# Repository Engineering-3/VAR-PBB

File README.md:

# VAR-PBB
Power Bus Board, but for variable uses

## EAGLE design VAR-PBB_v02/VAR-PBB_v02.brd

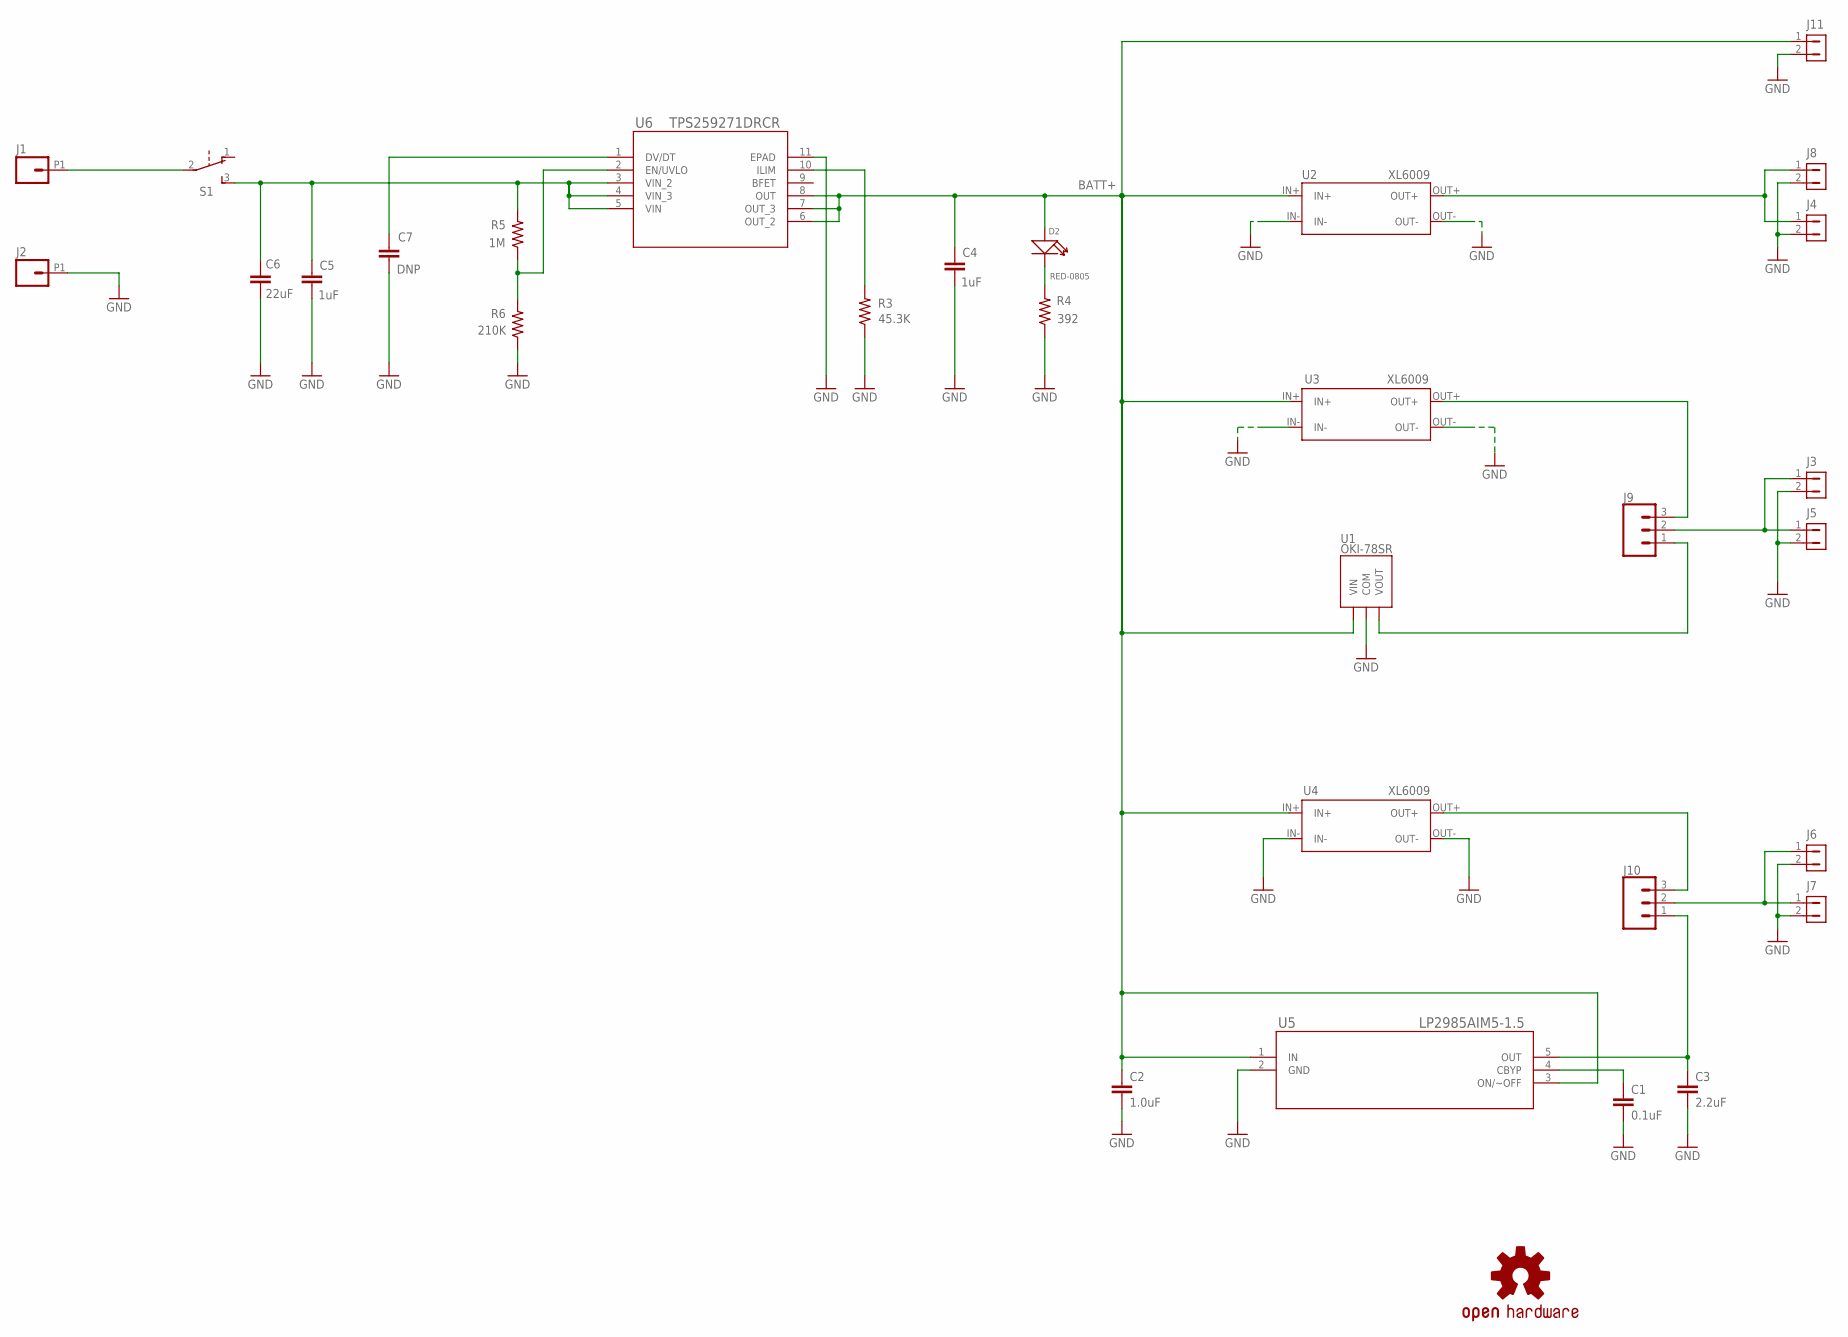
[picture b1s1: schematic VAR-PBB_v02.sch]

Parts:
C1: 0.1uF; 0603
C2: 1.0uF; 0603
C3: 2.2uF; 0603
C4, C5: 1uF; 0603
C6: 22uF; 1210
C7: DNP; 0603
D2: RED-0805; LED-0805
J1, J2: ANDERSON_POWER_POLE
J3, J4, J5, J6, J7, J8, J11: CON1X2_SHROUDED; HEADER_1X2_SHROUDED
J9, J10: CONN_03; 1X03
LOGO2: OSHW-LOGOM; OSHW-LOGO-M
R3: 45.3K; 0603
R4: 392; 0603
R5: 1M; 0603
R6: 210K; 0603
S1: SWITCH_SLIDE_ON_ON; SWITCH_SLIDE_RA
U1: OKI-78SR; OKI-78SR_REGULATOR_HORIZONTAL
U2, U3, U4: XL6009; XL6009_MODULE
U5: LP2985AIM5-1.5; MF05A
U6: TPS259271DRCR; DRC10_1P65X2P40
U$6: ROHS_GARBAGE; ROHS_GARBAGE_5MM

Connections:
1.5V_REG: C3.1, J10.1, U5.5 (OUT)
5V_REG: J9.1, U1.P$3 (VOUT)
BATT+: C2.1, C4.2, D2.+, J11.1, U1.P$1 (VIN), U2.IN+, U3.IN+, U4.IN+, U5.1 (IN), U5.3 (ON/~OFF), U6.6 (OUT_2), U6.7 (OUT_3), U6.8 (OUT)
CHANNEL3: J3.1, J5.1, J9.2
CHANNEL4: J6.1, J7.1, J10.2
GND: C1.2, C2.2, C3.2, C4.1, C5.1, C6.2, C7.1, J2.P1, J3.2, J4.2, J5.2, J6.2, J7.2, J8.2, J11.2, R3.1, R4.1, R6.1, U1.P$2 (COM), U2.IN-, U2.OUT-, U3.IN-, U3.OUT-, U4.IN-, U4.OUT-, U5.2 (GND), U6.11 (EPAD)
unnamed: C5.2, C6.1, R5.2, S1.3 (S), U6.3 (VIN_2), U6.4 (VIN_3), U6.5 (VIN)
unnamed: D2.-, R4.2
unnamed: J9.3, U3.OUT+
unnamed: R5.1, R6.2, U6.2 (EN/UVLO)
unnamed: J4.1, J8.1, U2.OUT+
unnamed: J10.3, U4.OUT+
unnamed: C1.1, U5.4 (CBYP)
unnamed: J1.P1, S1.2
unnamed: R3.2, U6.10 (ILIM)
unnamed: C7.2, U6.1 (DV/DT)

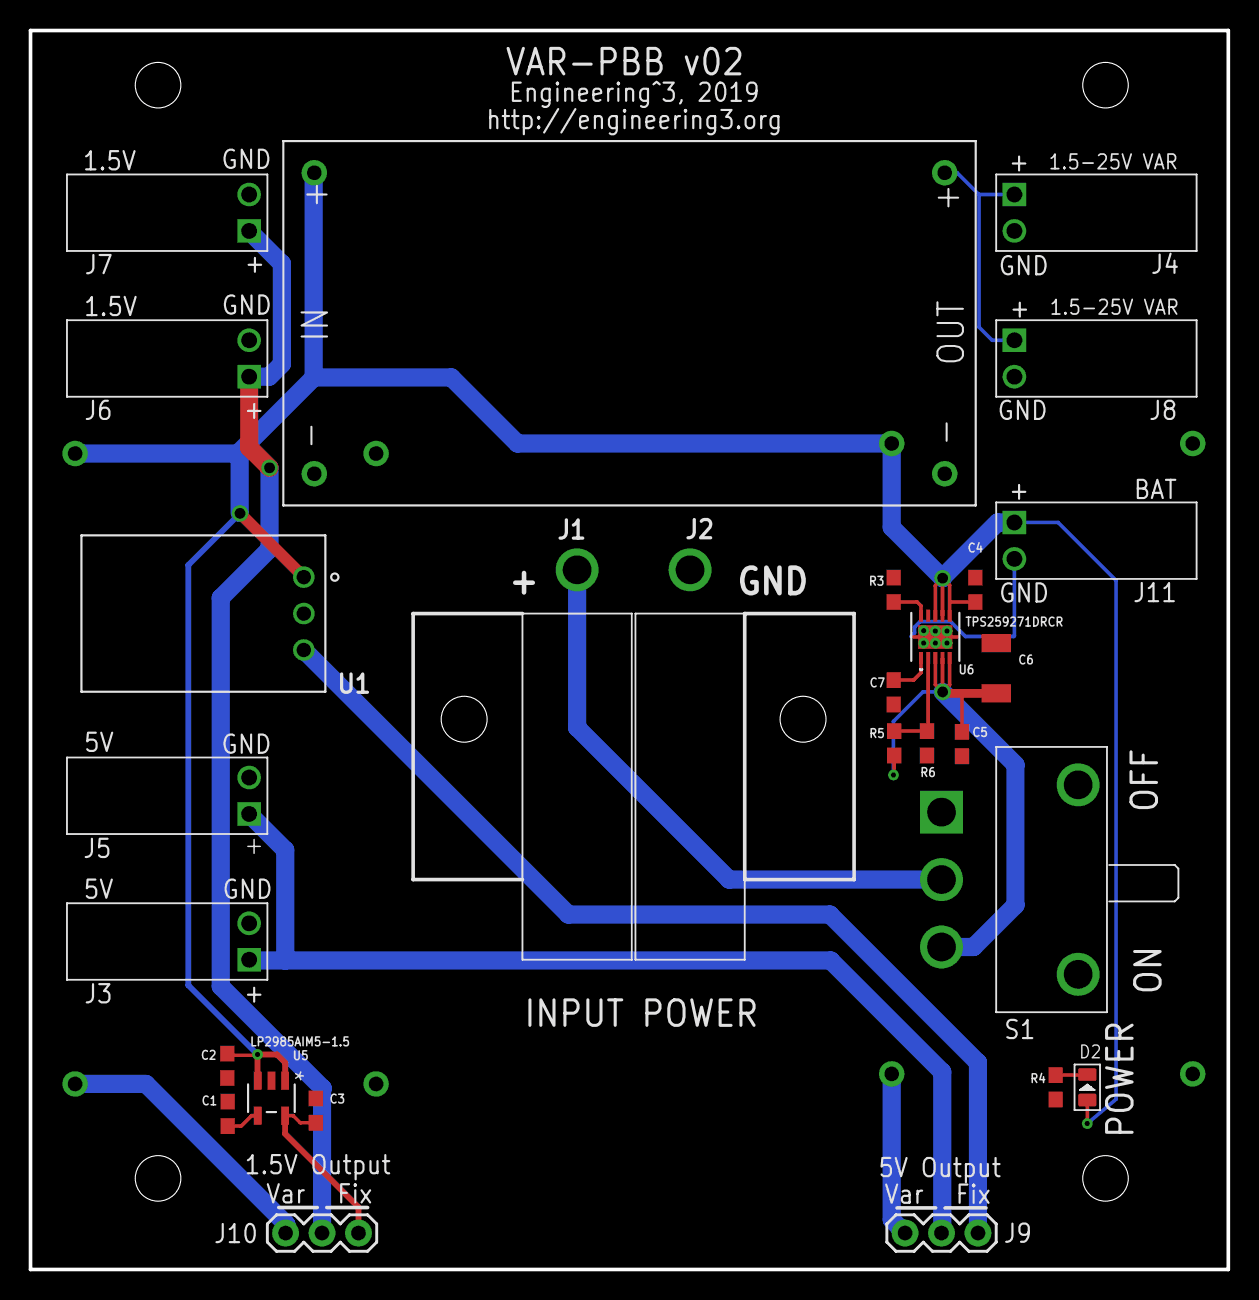
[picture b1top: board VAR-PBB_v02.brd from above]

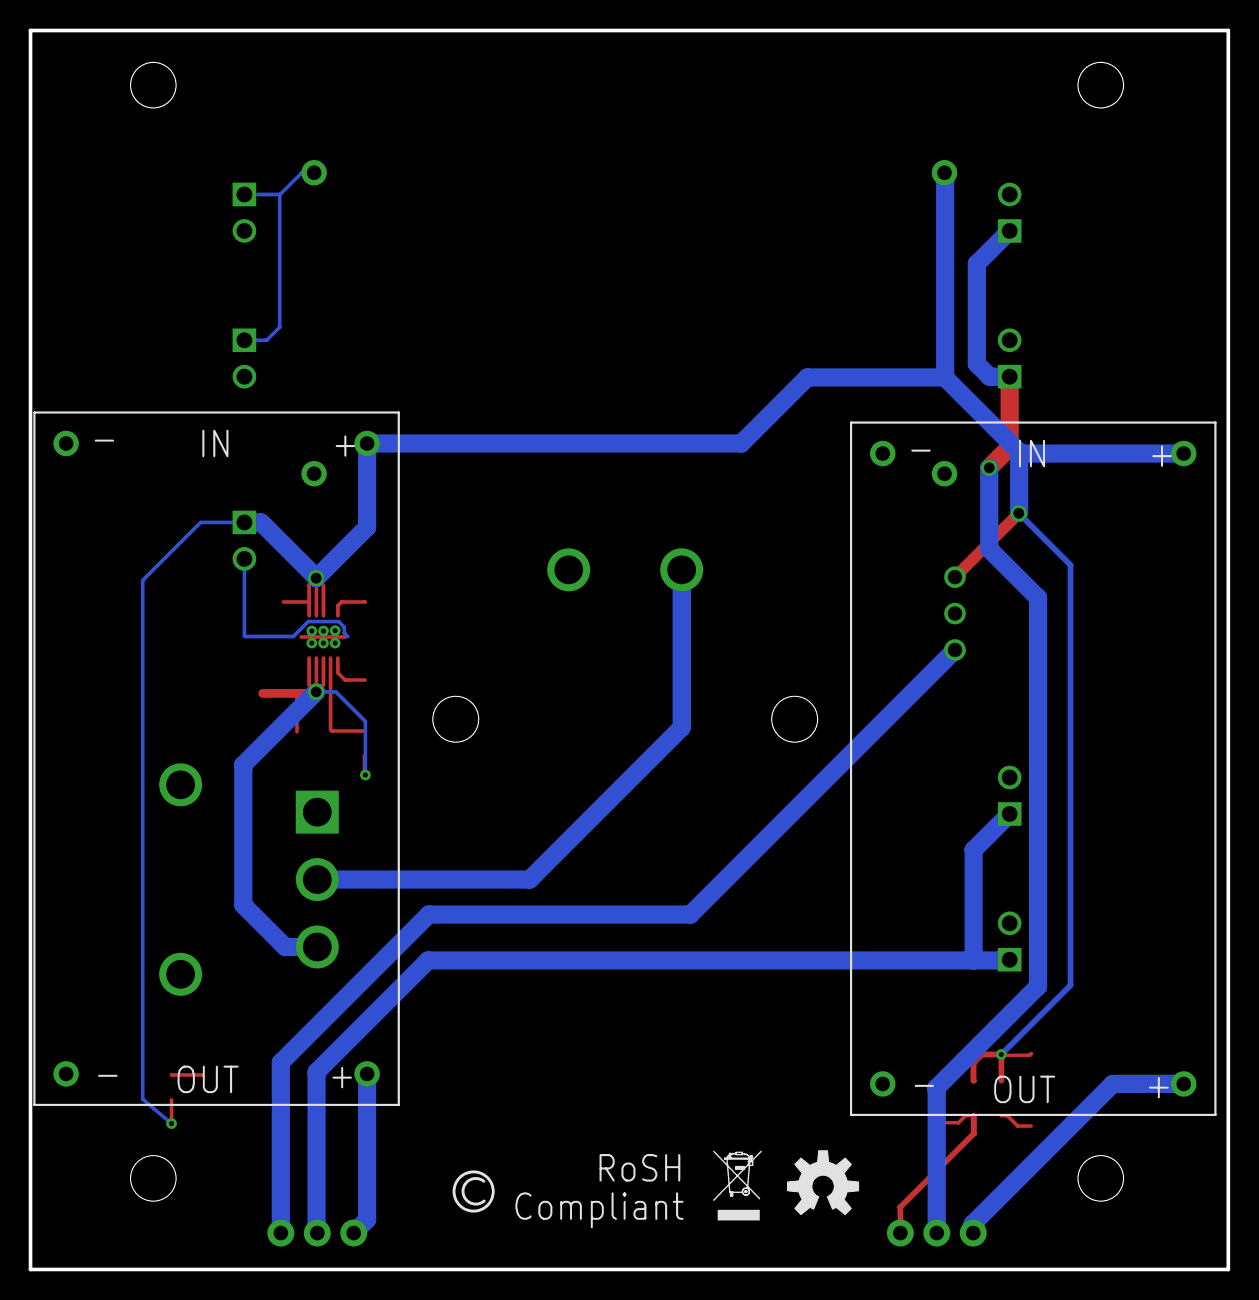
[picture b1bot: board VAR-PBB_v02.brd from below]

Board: 2 copper layers, 83.5 x 86.4 mm, 32 parts (4 on the bottom side), 16 nets.

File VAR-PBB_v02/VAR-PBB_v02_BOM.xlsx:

VAR-PBB | Rev 02
Schmalz Haus LLC
Brian Schmalz - brian@schmalzhaus.com
Reference Designator | Value | MFR | MFR Part Number | Digikey Part Number | Qty | Description | Notes
U1 |  | Murata Power Solutions Inc. | OKI-78SR-5/1.5-W36H-C | 811-2692-ND | 1 | Linear Regulator Replacement DC DC Converter 1 Output 5V 1.5A 7V - 36V Input | 5V fixed DC-DC switching regulator, right angle style
U5 |  | Texas Instruments | LP2985AIM5-1.5/NOPB | LP2985AIM5-1.5/NOPBCT-ND | 1 | Linear Voltage Regulator IC 1 Output 150mA SOT-23-5 | 1.5V linear low dropout regulator, SOT-23-5
D2 |  | Visual Communications Company - VCC | CMD17-21SRC/TR8 | L62411CT-ND | 1 | Red LED Indication - Discrete 1.7V 0805 (2012 Metric) | Super bright red LED 0805
U6 |  | Texas Instruments | TPS259271DRCR | 296-44973-1-ND | 1 | Electronic Fuse Regulator 5A 10-VSON (3x3) | E-fuse, UVLO and over-current cutout
U2 |  | Amazon | XL6009 DC to DC |  | 1 |  | https://www.amazon.com/gp/product/B07NTXSJHB/ref=ppx_yo_dt_b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
J1 |  | Anderson Power Products, Inc. | 1327 | 2243-1327-ND | 1 | 1 Position Blade Type Power Housing Connector Non-Gendered Red | Battery input power connector, RED
J2 |  | Anderson Power Products, Inc. | 1327G6-BK | 2243-1327G6-BK-ND | 1 | 1 Position Blade Type Power Housing Connector Non-Gendered Black | Battery input power connector, BLACK
 |  | Anderson Power Products, Inc. | 1399G8-BK | 2243-1399G8-BK-ND | 2 | PP10/45 MOUNTING WING BLUE | Power pole blue wings
 |  | Anderson Power Products, Inc. | 1377G4-BK | 2243-1377G4-BK-ND | 2 | Blade Contact Solder, PCB Non-Gendered Tin | Anderson power connector straight pins
S1 |  | E-Switch | 500SSP1S1M6QEA | EG2478-ND | 1 | Slide Switch SPDT Through Hole, Right Angle | Power slide switch
C6 |  | KEMET | C1210C226K4PACTU | 399-5092-1-ND | 1 | 22µF ±10% 16V Ceramic Capacitor X5R 1210 (3225 Metric) | 22uF 1210 16V ceramic cap
C2, C4, C5 |  | Murata Electronics | GRT188C8YA105KE13D | 490-12297-1-ND | 2 | 1µF ±10% 35V Ceramic Capacitor X6S 0603 (1608 Metric) | 1uF 0603 >30V ceramic cap
R3 |  | Stackpole Electronics Inc | RMCF0603FT45K3 | RMCF0603FT45K3CT-ND | 1 | 45.3 kOhms ±1% 0.1W, 1/10W Chip Resistor 0603 (1608 Metric) Automotive AEC-Q200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 | 45.3K 1% 0603 resistor
R5 |  | Stackpole Electronics Inc | RMCF0603FG1M00 | RMCF0603FG1M00CT-ND | 1 | 1 MOhms ±1% 0.1W, 1/10W Chip Resistor 0603 (1608 Metric) Automotive AEC-Q200 Th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 | 1M 1% 0603 resistor
R6 |  | Stackpole Electronics Inc | RMCF0603FT210K | RMCF0603FT210KCT-ND | 1 | 210 kOhms ±1% 0.1W, 1/10W Chip Resistor 0603 (1608 Metric) Automotive AEC-Q200 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 | 210K 1% 0603 resistor
R4 |  | Stackpole Electronics Inc | RNCP0603FTD392R | RNCP0603FTD392RCT-ND | 1 | 392 Ohms ±1% 0.125W, 1/8W Chip Resistor 0603 (1608 Metric) Anti-Sulfur, Moistur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 | 392 ohm 0603 resistor
J11, J8, J4, J3, J5 J6, J7 |  | Molex | 70553-0036 | WM4924-ND | 7 | Connector Header Through Hole, Right Angle 2 position 0.100" (2.54mm) | 2-pin polarized power output connectors
C1 |  | KEMET | C0603C104M5RACTU | 399-7845-1-ND | 1 | 0.1µF ±20% 50V Ceramic Capacitor X7R 0603 (1608 Metric) | .1uF 0603 cap
C3 |  | Murata Electronics | GRM188R6YA225MA12D | 490-10486-1-ND | 1 | 2.2µF ±20% 35V Ceramic Capacitor X5R 0603 (1608 Metric) | 2.2uF 0603 cap
J9, J10 |  | Adam Tech | PH1-03-UA | 2057-PH1-03-UA-ND | 2 | Connector Header Through Hole 3 position 0.100" (2.54mm) | 3-pin 0.1" male headers
JMP1, JMP2 |  | Sullins Connector Solutions | SPC02SYAN | S9001-ND | 2 | 2 (1 x 2) Position Shunt Connector Black Closed Top 0.100" (2.54mm) Gold | 2-pin 0.1" jumper shorting blocks
DO NOT POPULATE
C7 |  |  |  |  |  |  | Unknown value 0603 ceramic cap
U3, U4 |  | Amazon | XL6009 DC to DC |  | 2 |  | https://www.amazon.com/gp/product/B07NTXSJHB/ref=ppx_yo_dt_b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

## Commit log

2019-12-28 First checkin. WIP.
2019-12-30 WIP, but got a ton done.
2019-12-31 Got all of the features in, board layout done, silk screen tweaked. Need to pick resistor values for UVLO and dV/dT, power LED, and finish BOM xls.
2020-01-02 v01 done - schematic complete and cleaned up, board fully routed, passes DRC, BOM complete.
2020-01-31 Latest version of VAR-PBB, as built. Updated under voltage cutout resistor to get UVLO to around 8.1 V.
2020-10-31 Fixed misspelled top silk text "Engineering" to create v2.0 design.

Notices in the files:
VAR-PBB_v02/VAR-PBB_v02.sch:
Copyright 2019 Engineering^3 LLC Copyright and related rights are licensed under the Solderpad Hardware License,
Version 0.51 (the “License”); you may not use this file except in compliance with the License. You may obtain a copy
of the License at http://solderpad.org/licenses/SHL-0.51. Unless required by applicable law or agreed to in writing,
software, hardware and materials distributed under this License is distributed on an “AS IS” BASIS, WITHOUT
Copyright 2020 Engineering^3 LLC
